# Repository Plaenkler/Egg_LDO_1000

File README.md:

# Egg LDO 1000

> No AI was involved in this project. Whether that is a mark of quality or the opposite is up to you.

<table>
  <tr>
    <td></td>
    <td></td>
  </tr>
</table>

## 📖 About the EGG LDO 1000

The EGG LDO 1000 is an expansion of the modular EGG design series, representing a larger model within the portfolio. The EGG series consists of a variety of modules that can be used independently and are based on different PCB designs.
Unlike the LDO 250, the LDO 1000 is designed to handle higher current applications, offering a linear voltage regulator capable of delivering up to 1000 mA.
In this model, the XC6220B331MR-G voltage regulator is utilized, providing a stable output of 3.3V and supporting a load of up to 1000 mA.
This makes it significantly more suitable for higher power requirements compared to the LDO 250.
It also features overcurrent protection and thermal shutdown for enhanced safety.

## ⚡ Circuit Diagram

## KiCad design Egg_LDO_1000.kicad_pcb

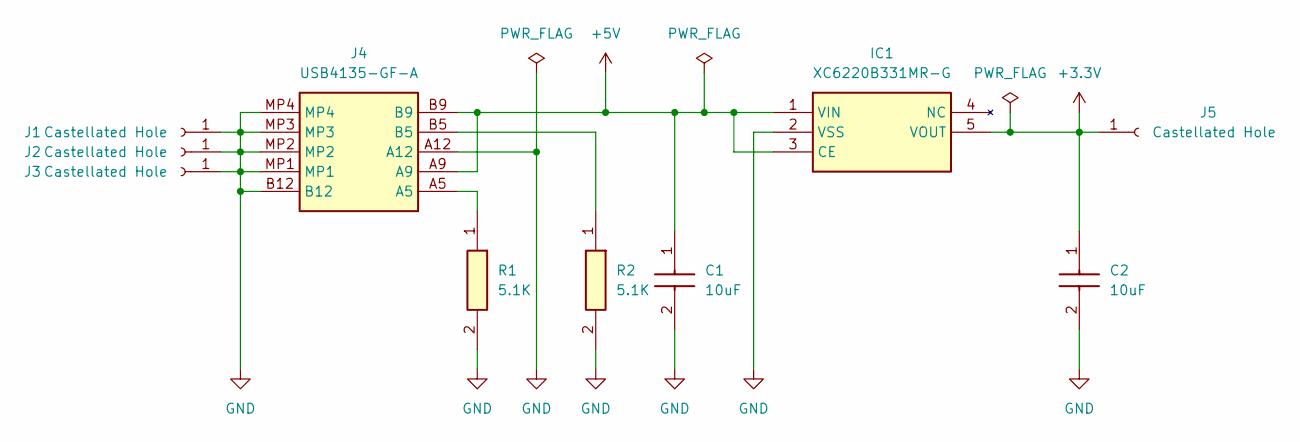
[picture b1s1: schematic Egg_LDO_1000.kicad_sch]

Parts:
C1, C2: 10uF; C0603; Mouser Part Number 80-C0603C106M8PLR
IC1: XC6220B331MR-G; SOT95P280X130-5N; Mouser Part Number 865-XC6220B331MR-G
J1, J2, J3, J5: Castellated Hole; PinHeader_1x01_P2.54mm_Vertical
J4: USB4135-GF-A; USB4135GFA; Mouser Part Number 640-USB4135-GF-A
R1, R2: 5.1K; ERJUP3; Mouser Part Number 667-ERJ-UP3J512V

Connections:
+3.3V: C2.1, IC1.5 (VOUT), J5.1
+5V: C1.1, IC1.1 (VIN), IC1.3 (CE), J4.A9, J4.B9
GND: C1.2, C2.2, IC1.2 (VSS), J1.1, J2.1, J3.1, J4.A12, J4.B12, J4.MP1, J4.MP2, J4.MP3, J4.MP4, R1.2, R2.2
unnamed: J4.A5, R1.1
unnamed: J4.B5, R2.1

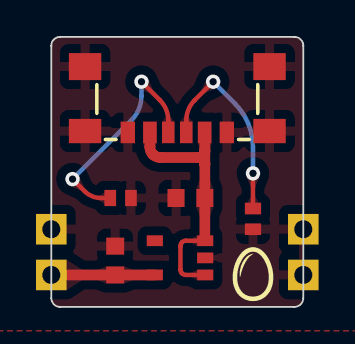
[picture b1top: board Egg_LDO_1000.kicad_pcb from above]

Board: 2 copper layers, 14.0 x 15.0 mm, 10 parts (0 on the bottom side), 5 nets.

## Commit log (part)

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2024-01-23 [ADD] Current state
2024-01-23 [ADD] Interactive BOM
2024-01-23 [UPD] v1.0.0
2024-01-23 [FIX] Center pads on edge
2024-01-23 [UPD] DRC exclude starved_thermal
2024-01-23 [FIX] Name 1000
2024-01-23 [FIX] Location 10uF
2024-01-23 [FIX] Net caps reference
2024-01-23 [FIX] Bump version
    Regarding ad04070
2024-01-24 [ADD] README.md
2024-02-14 [FIX] Remove pin headers
2024-02-14 [ADD] Step file
2024-02-14 [ADD] Footprint
2024-02-14 [ADD] Symbol
2024-02-14 [UPD] Symbol pins
2024-02-14 [UPD] Symbol bg filled
2024-02-14 [REM] 3D Pins
2024-03-04 [BCH] Migrated to KiCad8 & added teardrops
2024-03-04 [FIX] Name Egg_LDO_1000.step
2024-03-04 [UPD] Round traces
2024-03-05 [ADD] Alternative tag mpn
2024-03-05 [UPD] Bumped PCB version
2024-03-05 [UPD] README.md
